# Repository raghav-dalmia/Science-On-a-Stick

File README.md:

# Science-On-a-Stick
Science on a Stick, as the name suggests, it is an experimental setup based on Python and Arduino, was developed to verify various laws of Physics such as Lenz's Law, Faraday's Law and Laws of Motion.

We have provided schematics of circuits and code for this project.

# Installation

## To install Arduino IDE
Click [here](https://www.arduino.cc/en/Main/Software) to download Arduino IDE.

## To setup up Python Environment
To download Python IDE, click [here](https://www.python.org/downloads/release/python-2715/).

**Note:-** t would be preferable to download the latest version Python2.7.

### To set up environment variables
----
**Windows 10 and Windows 8**

1. In Search, search for and then select: System (Control Panel)

2. Click the Advanced system settings link.

3. Click Environment Variables. In the section System Variables, find the PATH environment variable and select it. Click Edit. If the PATH environment variable does not exist, click New.

4. In the Edit System Variable (or New System Variable) window, specify the value (location of the folder where python installed) of the PATH environment variable. Click OK. Close all remaining windows by clicking OK.

5. Open Command prompt window, and run following command:
    
       python --version
       pip --version
       
 If pip is not installed in your laptop, refer [this.](https://github.com/pypa/get-pip)
## Install dependencies of python code
open Command prompt or terminal and run this command
    
    pip install pyserial
    pip install matplotlib
    pip install numpy

## To Install Eagle
Download Eagle (PCB design software) from this [link.](https://www.autodesk.in/products/eagle/free-download?referrer=%2Fproducts%2Feagle%2Ffree-download)

Open the given board layouts and fabricate them. The schematic folder has three schematics and their board layouts. 

**Images of Fabricated Board and coil**
---------------------------------------

**!! More than 1000 turns (36 gauge copper wire) of coil winding can destroy the circuit**

# Usage

## Law's of MOtion

Set the experimental tube as shown in [picture.](https://github.com/raghav-dalmia/Science-On-a-Stick/blob/master/Images/Law's%20of%20Motion%20Setup.jpeg)

1. open Arduino IDE and upload `Laws_of_Motion` code.

2. For law's motion open the serial monitor and enter values asked by monitor.

**Output**
----------
.jpeg)

## Lenz's Law

Set the experimental setup as shown in [picture.](https://github.com/raghav-dalmia/Science-On-a-Stick/blob/master/Images/Lenz's%20Law%20Setup.jpeg)

1. Open Arduino IDE and upload `Lenz_s_Law_Arduino` code.
2. Open python code and change com port value(in Windows its `com5`, in Linux its `/dev/ttyUSB0`)
    
       arduinoData=serial.Serial('com5',115200)
3. Open Command prompt or terminal and  change current working directory to directory of this python code using
         
       cd <complete-path>
4. Run python code by the following command

       python "Lenz's_Law_Python.py"
   
**Output**
----------

.png)
       
# Credits
This experimental setup is developed under the guidance of Prof. D.V. Gadre, Director CEDT, NSUT.

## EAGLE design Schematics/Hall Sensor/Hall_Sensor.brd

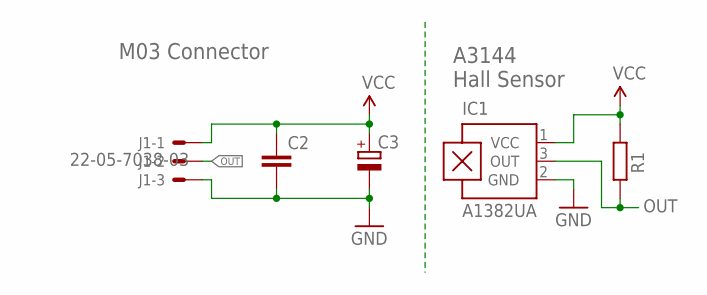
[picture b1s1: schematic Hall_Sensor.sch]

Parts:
C2: C-EU025-025X050; C025-025X050
C3: CPOL-EUE2,5-6E; E2,5-6E
IC1: A1382UA; SIP3-UA
J1: 22-05-7038-03; 7395-03
R1: R-EU_0207/7; 0207/7

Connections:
GND: C2.2, C3.-, IC1.2 (GND), J1.3
OUT: IC1.3 (OUT), J1.2, R1.1
VCC: C2.1, C3.+, IC1.1 (VCC), J1.1, R1.2

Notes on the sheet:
M03 Connector
A3144 Hall Sensor

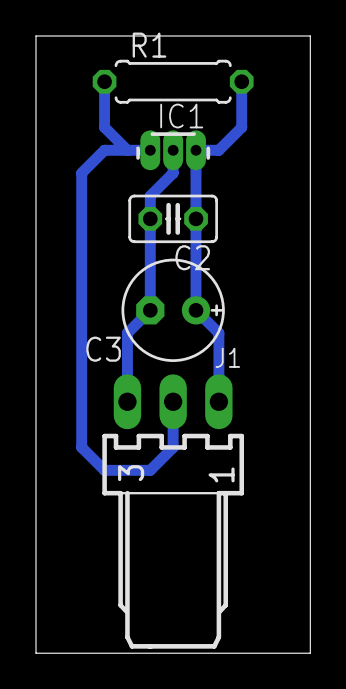
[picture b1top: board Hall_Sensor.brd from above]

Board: 2 copper layers, 15.2 x 34.3 mm, 5 parts (0 on the bottom side), 3 nets.

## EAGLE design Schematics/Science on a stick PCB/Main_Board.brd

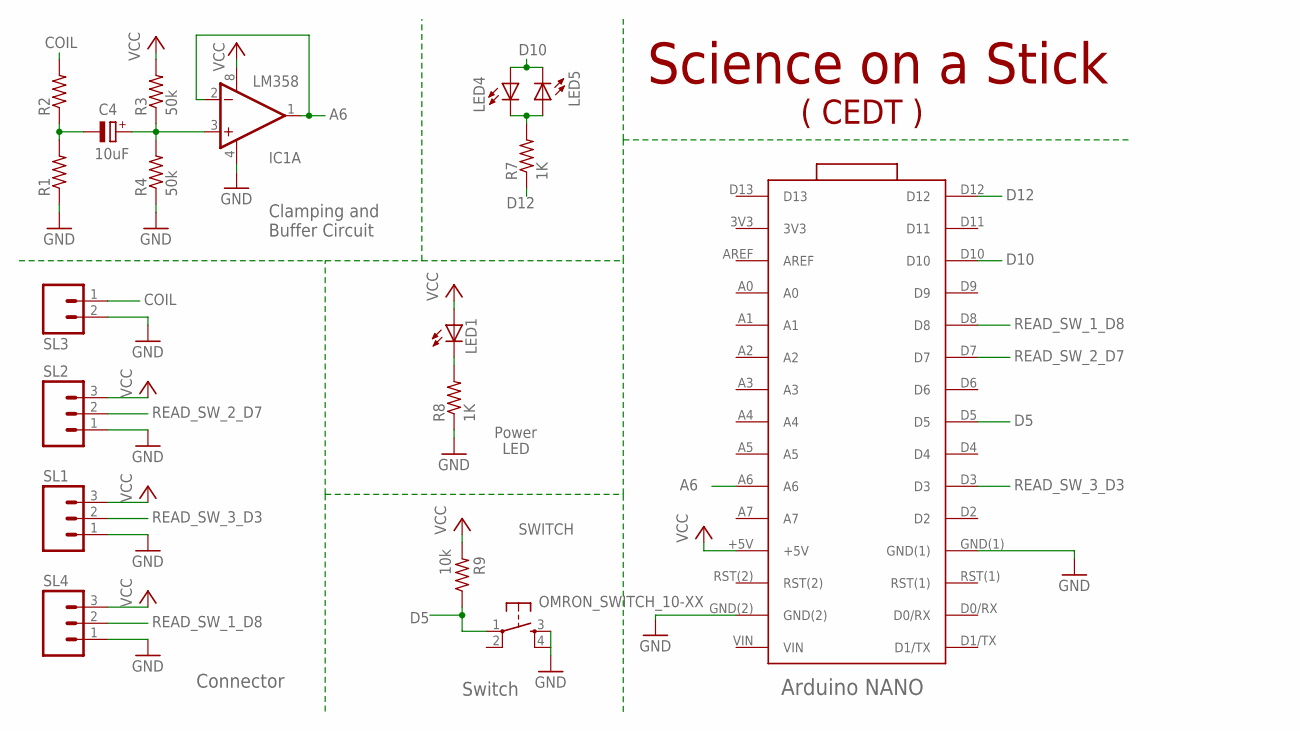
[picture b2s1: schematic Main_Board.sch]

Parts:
C4: 10uF; E2,5-5
IC1: LM358; DIP08
LED1, LED4, LED5: LED3MM
R1, R2: RESISTOR0207/7; 0207/7
R3, R4: 50k; 0207/7
R7, R8: 1K; 0207/7
R9: 10k; 0207/7
SL1, SL2, SL4: M03; 03P
SL3: M02; 02P
SWITCH: OMRON_SWITCH_10-XX; B3F-10XX
U$1: ARDUINO_NANO_3_ARDUINO(NANO_3.0); ARDUINO_NANO_3_ARDUINO_NANO_30PIN

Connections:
A6: IC1.1 (OUT), IC1.2 (-IN), U$1.A6
CLAMP_SIGNAL: C4.+, IC1.3 (+IN), R3.1, R4.2
COIL: R2.2, SL3.1
D5: R9.1, SWITCH.1, U$1.D5
D10: LED4.A, LED5.K (C), U$1.D10
D12: R7.1, U$1.D12
GND: IC1.4 (V-), R1.1, R4.1, R8.1, SL1.1, SL2.1, SL3.2, SL4.1, SWITCH.3 (S), SWITCH.4 (S1), U$1.GND(1), U$1.GND(2)
unnamed: C4.-, R1.2, R2.1
unnamed: LED1.K (C), R8.2
unnamed: LED4.K (C), LED5.A, R7.2
READ_SW_1_D8: SL4.2, U$1.D8
READ_SW_2_D7: SL2.2, U$1.D7
READ_SW_3_D3: SL1.2, U$1.D3
VCC: IC1.8 (V+), LED1.A, R3.2, R9.2, SL1.3, SL2.3, SL4.3, U$1.+5V

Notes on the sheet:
Arduino NANO
Science on a Stick
( CEDT )
Power
LED
Switch
Connector
Clamping and Buffer Circuit

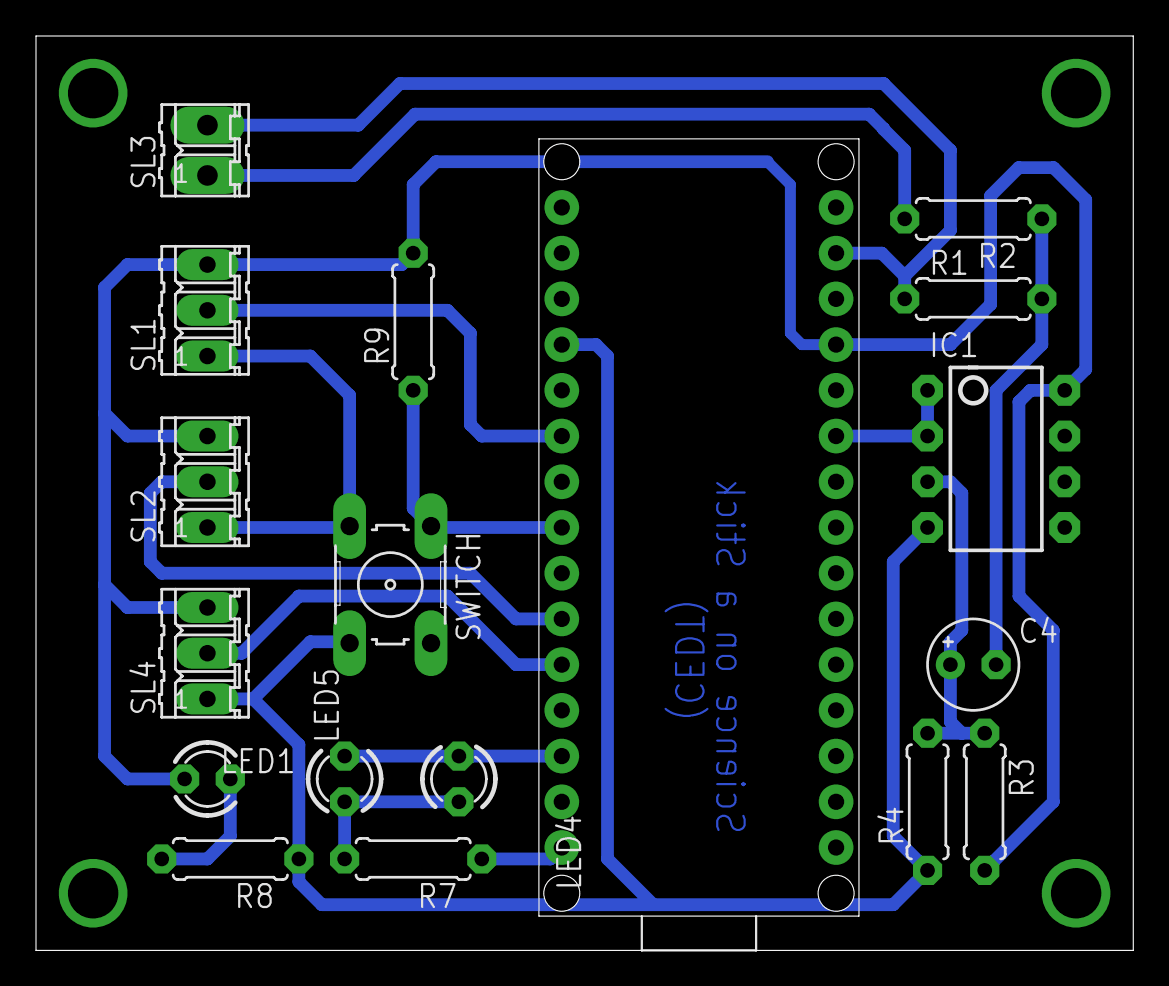
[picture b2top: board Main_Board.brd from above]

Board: 2 copper layers, 61.0 x 50.8 mm, 18 parts (0 on the bottom side), 14 nets.

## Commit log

2019-01-27 Board Layouts and Schematics
2019-01-27 Code for Lenz's Law
2019-01-27 code for Law's of Motion
2019-01-27 Images of setup and output
2019-01-27 circuit of Magnetic Sensor
2019-01-27 Image of setup and output
2019-01-27 Setup and output images
2019-01-27 delete
2019-01-27 Add images in ReadMe
2019-02-05 Set theme jekyll-theme-leap-day

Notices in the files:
parts and their libraries:
SparkFun-AnalogIC: Licensing:Creative Commons ShareAlike 4.0 International - https://creativecommons.org/licenses/by-sa/4.0
